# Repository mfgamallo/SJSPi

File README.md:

# SJSPi
Send signals to a Sinclair joystick port from a Raspberry Pi.

The Spectrum +2A and +3 come with two special joystick ports. They look like Atari, but aren't.

This projects presents a board and some code so any gamepad usable in a Raspberry Pi can be used to drive those ports.

Make it work:

$ cd python
$ python3 -m venv ./venv
$ . ./venv/bin/activate
$ pip3 install evdev
$ pip3 install rpi.gpio
$ python3 main.py

To make it autostart on the Pi:

Clone project in /home/pi/SJSPi
Use sjspi.service to install systemd service

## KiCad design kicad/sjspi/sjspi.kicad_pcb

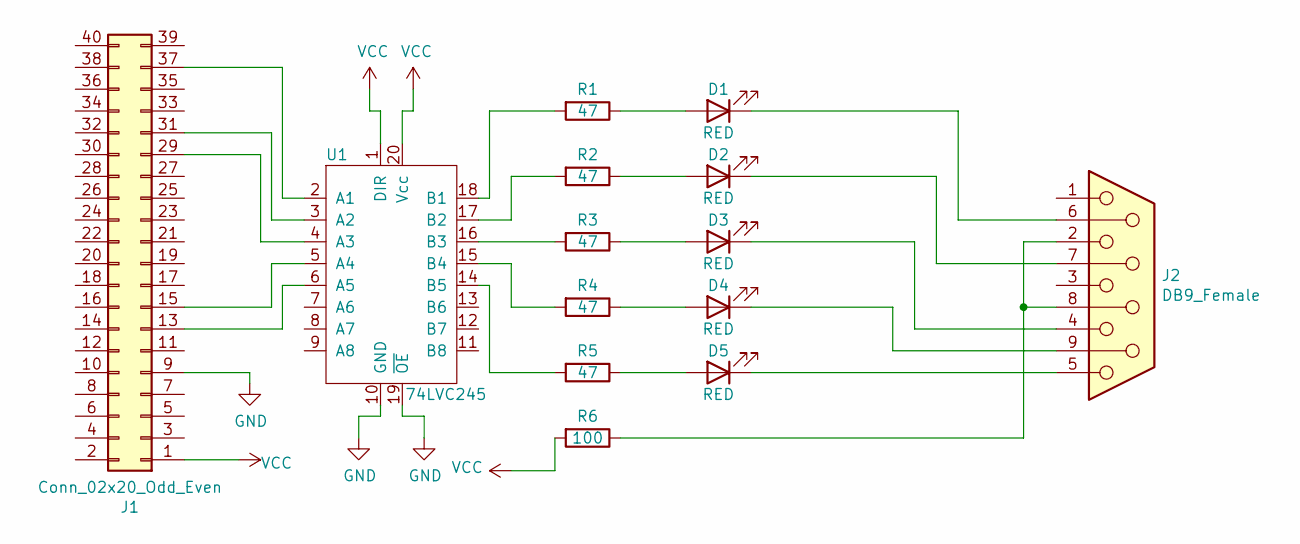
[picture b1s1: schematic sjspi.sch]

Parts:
D1, D2, D3, D4, D5: RED; LED_D5.0mm
J1: Conn_02x20_Odd_Even; PinSocket_2x20_P2.54mm_Vertical
J2: DB9_Female; DSUB-9_Female_Horizontal_P2.77x2.84mm_EdgePinOffset7.70mm_H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
R1, R2, R3, R4, R5: 47; R_Axial_DIN0309_L9.0mm_D3.2mm_P12.70mm_Horizontal
R6: 100; R_Axial_DIN0309_L9.0mm_D3.2mm_P12.70mm_Horizontal
U1: 74LVC245; DIP-20_W7.62mm

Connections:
GND: J1.9, U1.10 (GND), U1.19 (~OE)
unnamed: D1.1 (K), J2.6
unnamed: D1.2 (A), R1.1
unnamed: D2.1 (K), J2.7
unnamed: D2.2 (A), R2.1
unnamed: D3.1 (K), J2.4
unnamed: D3.2 (A), R3.1
unnamed: D4.1 (K), J2.9
unnamed: D4.2 (A), R4.1
unnamed: D5.1 (K), J2.5
unnamed: D5.2 (A), R5.1
unnamed: J1.13, U1.6 (A5)
unnamed: J1.15, U1.5 (A4)
unnamed: J1.29, U1.4 (A3)
unnamed: J1.31, U1.3 (A2)
unnamed: J1.37, U1.2 (A1)
unnamed: J2.2, J2.8, R6.1
unnamed: R1.2, U1.18 (B1)
unnamed: R2.2, U1.17 (B2)
unnamed: R3.2, U1.16 (B3)
unnamed: R4.2, U1.15 (B4)
unnamed: R5.2, U1.14 (B5)
VCC: J1.1, R6.2, U1.1 (DIR), U1.20 (Vcc)

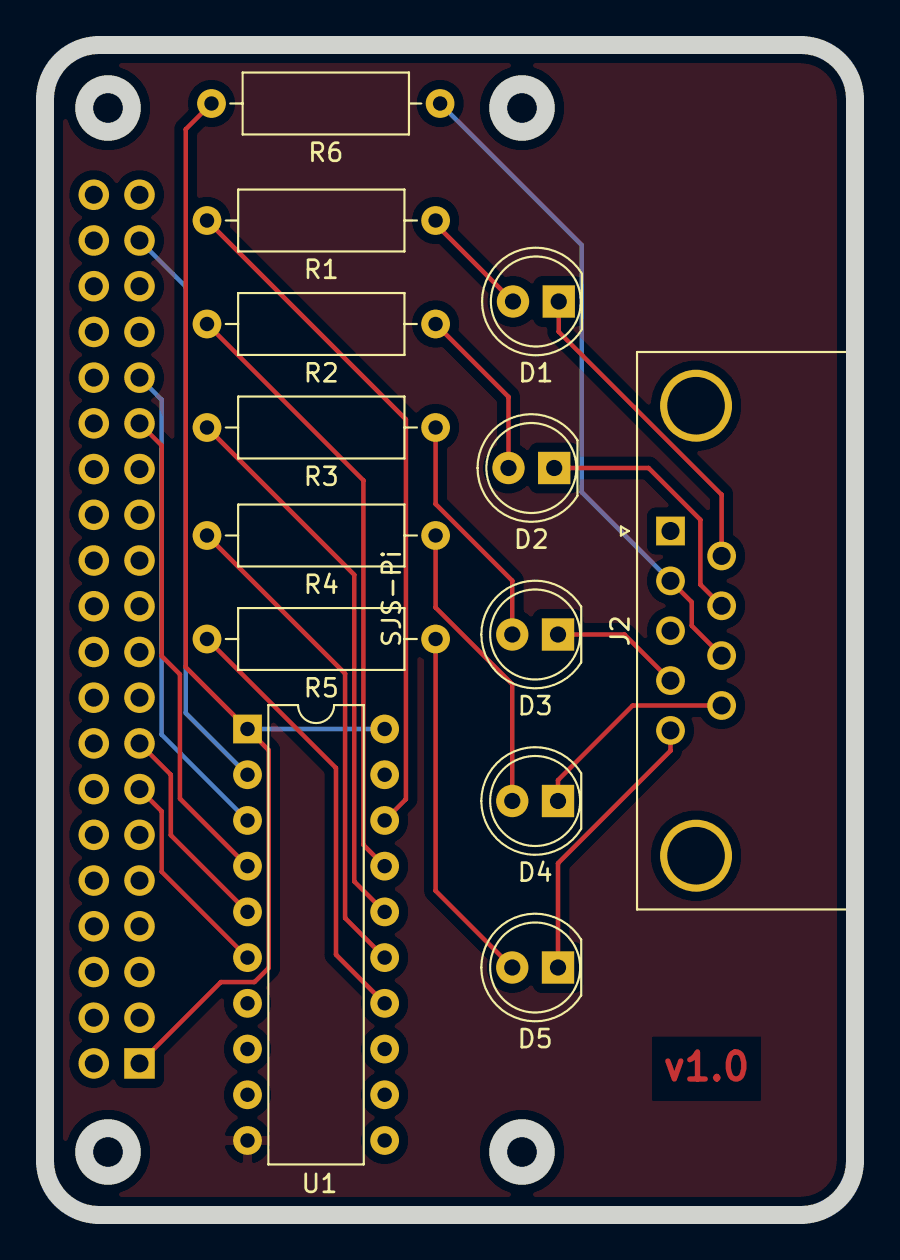
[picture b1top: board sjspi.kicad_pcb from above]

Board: 2 copper layers, 45.0 x 65.0 mm, 14 parts (1 on the bottom side), 23 nets.

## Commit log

2021-06-12 PCB v0.1
2021-06-21 v0.2 - fix pi connector position. Fix DB9 size. Connect level shifter's ground leg
2021-06-27 v0.3 - fix resistors values
2021-07-03 v1.0 - Release
2021-07-27 Code to drive the joystick ports
2021-07-27 Remove submodule
2021-07-27 Fix error. Improve readme
2021-07-27 Fix error
2021-07-27 Fix naming error
2021-07-28 Add systemd service. Update readme
2021-07-28 Update systemd service

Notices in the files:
kicad/sjspi/sjspi.kicad_pcb:
License: CC BY 4.0
kicad/sjspi/sjspi.sch:
creativecommons.org/licenses/by/4.0
